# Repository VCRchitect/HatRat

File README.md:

HatRat, the Mouse For Your Hat!
======

This project is an attempt to make an inexpensive, easy-to-use head mouse. The shell is 3D printed and features a clip to put it on a hat, visor, or maybe even a glasses frame. 

To use the device, clip it onto something with the USB C port facing outward toward the screen. Connect a USB cable and the device will automatically turn on. Move your head up, down, left, or right to move the mouse accordingly. 

How to Use the HatRat
======
If you hold still (or even just relatively still) for 3 seconds, the mouse will enter a gesture mode:
1.  Tilt left then back to center to left-click the mouse.
2.  Tilt right then back to center to right-click the mouse.
3.  To left-click and drag, tilt to the left and keep tilted. Move your head in the direction you want to drag while keeping your head tilted. When you're done, tilt your head back to the center.
4.  To right-click and drag, tilt to the right and keep tilted. Move your head in the direction you want to drag while keeping your head tilted. When you're done, tilt your head back to the center.

If you need to reset the orientation of the mouse, look to the edge of the screen. Like, if your head is too far turned to the left, just turn all the way to the right until you're about where you want "right" to be. The same holds true for up, down, left, and right.

If you're clicking and dragging and need to drop something with precision, hold your head still for the 3 seconds to freeze the mouse in place before you tilt the opposite direction to release the click.

In the repository is the Arduino sketch, 3D print files, and KiCAD files needed to build the thing.

Bill of Materials
======
Other than the circuit board, you will need:
-	1x Arduino Pro Micro USB C
-	1x Bidirectional Logic Level Converter
-	1x AMS1117-3.3V Voltage Regulator
-	1x MPU6050 Accelerometer
-	2x Female Headers - 12 Pins - 2.54mm Pitch

You should be able to print the thing with about 25g of filament, making the entire thing cost about $15, versus the hundreds of dollars that other solutions cost.

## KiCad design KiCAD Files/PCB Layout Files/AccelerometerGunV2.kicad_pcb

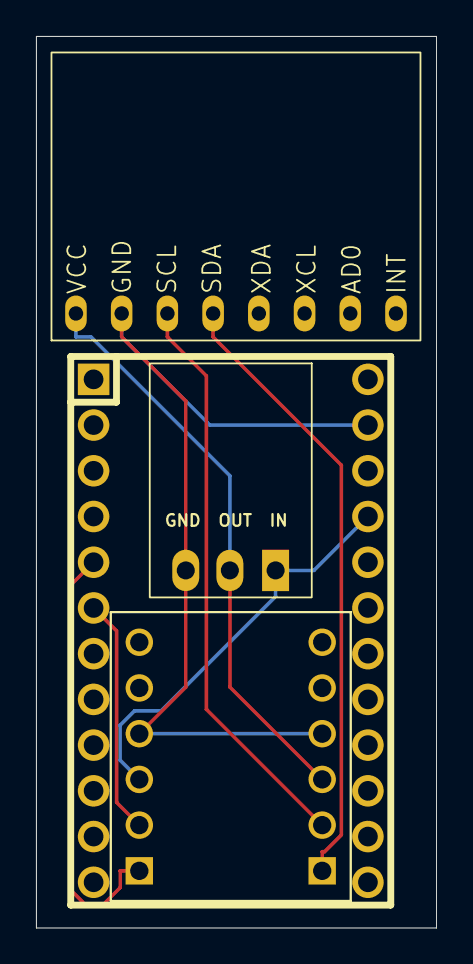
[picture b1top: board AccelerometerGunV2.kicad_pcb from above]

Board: 2 copper layers, 22.2 x 49.5 mm, 4 parts (0 on the bottom side), 7 nets.

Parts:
MPU1: MPU6050 Accelerometer
U1: ProMicro; ARDUINO_PRO_MICRO
U2: 3.3v InOutGnd Voltage Regulator
U3: BOB-12009; CONV_BOB-12009

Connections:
unnamed: MPU1.2 (GND), U1.23 (GND), U2.3 (GND), U3.GND_1 (GND), U3.GND_2 (GND)
unnamed: U1.21 (VCC), U2.1 (IN), U3.HV
unnamed: MPU1.3 (SCL), U3.LV2
unnamed: MPU1.4 (SDA), U3.LV1
unnamed: MPU1.1 (VCC), U2.2 (OUT), U3.LV
unnamed: U1.6 (SCL), U3.HV2
unnamed: U1.5 (SDA), U3.HV1

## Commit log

2025-03-22 Initial Commit of Files
    Here is everything you need to build a HatRat of your own!
2025-04-10 Slight Tweaks to the Code
2025-06-29 I THINK IT IS DONE
2025-07-06 Click and Drag Added
